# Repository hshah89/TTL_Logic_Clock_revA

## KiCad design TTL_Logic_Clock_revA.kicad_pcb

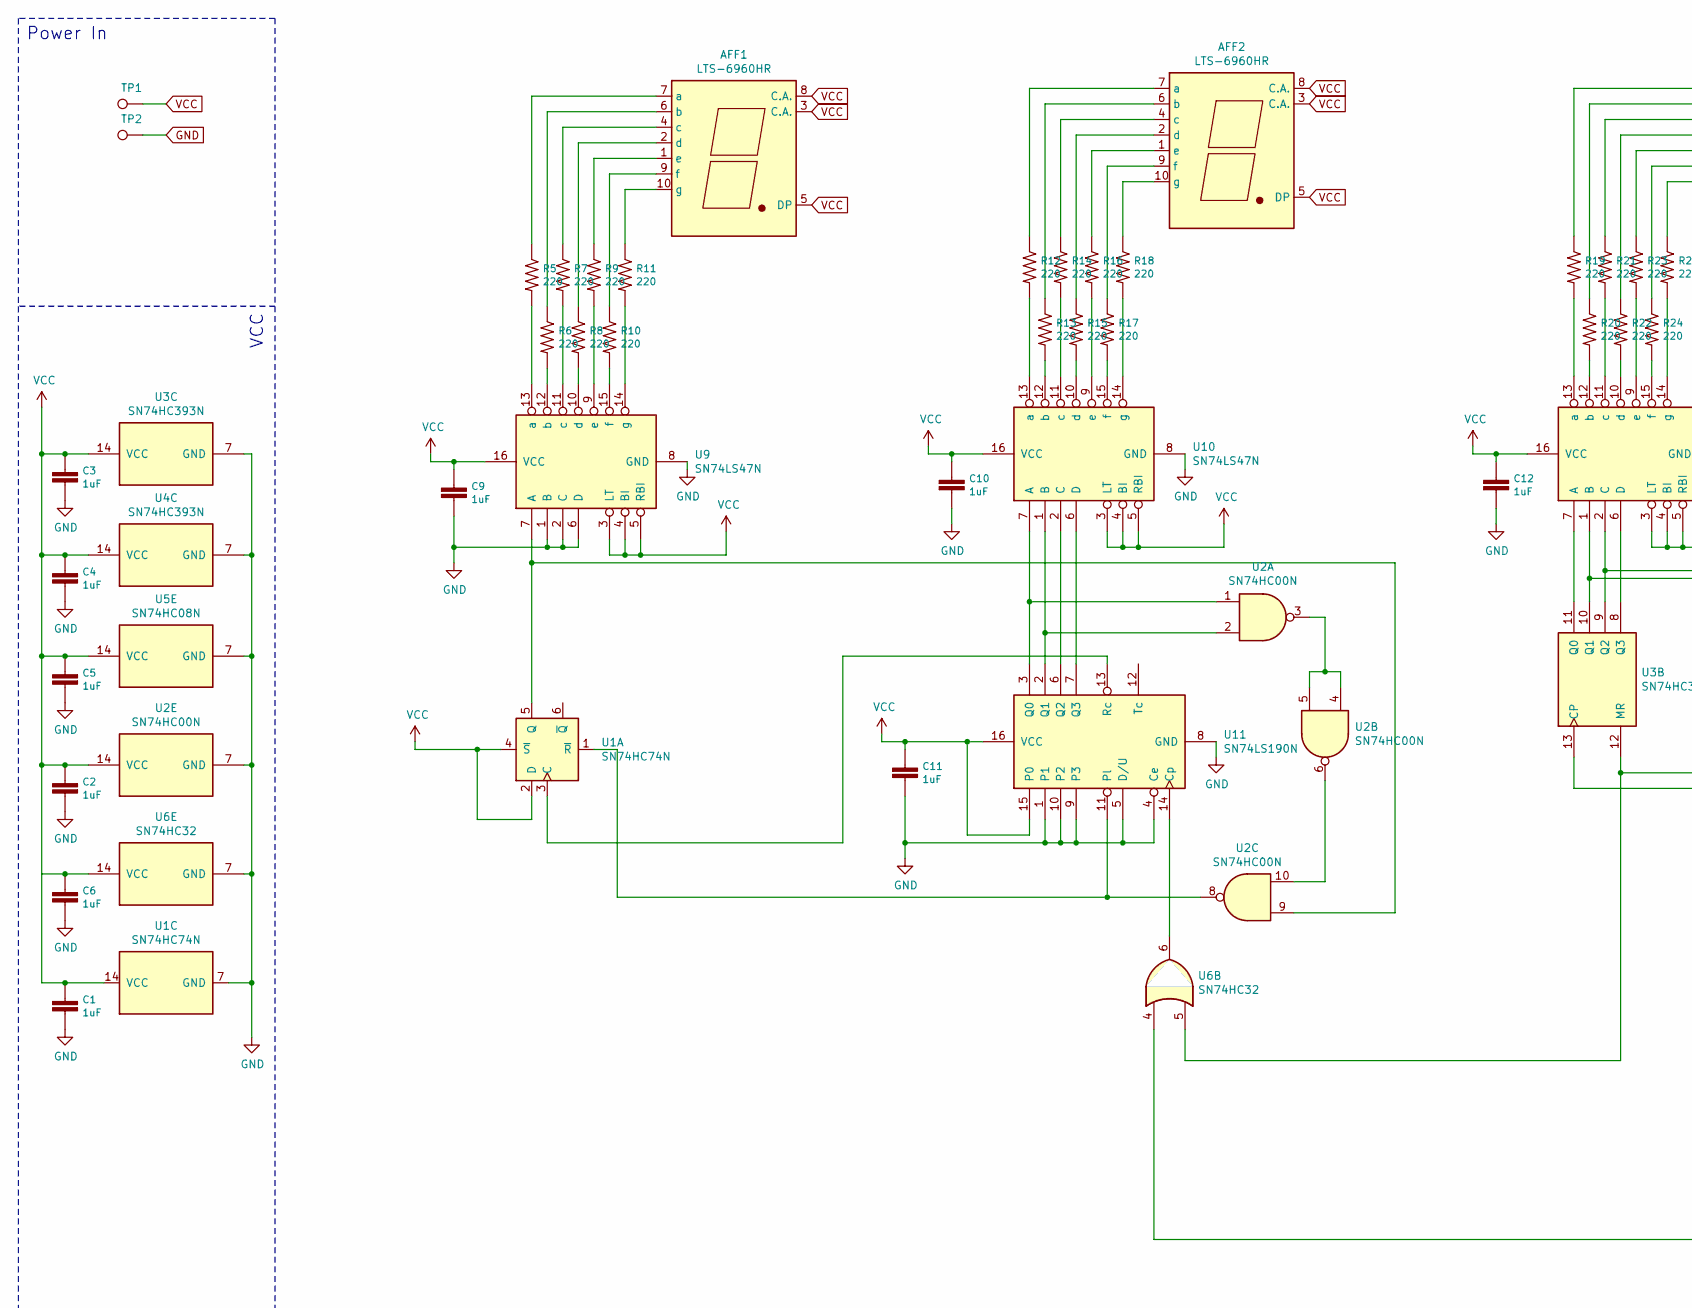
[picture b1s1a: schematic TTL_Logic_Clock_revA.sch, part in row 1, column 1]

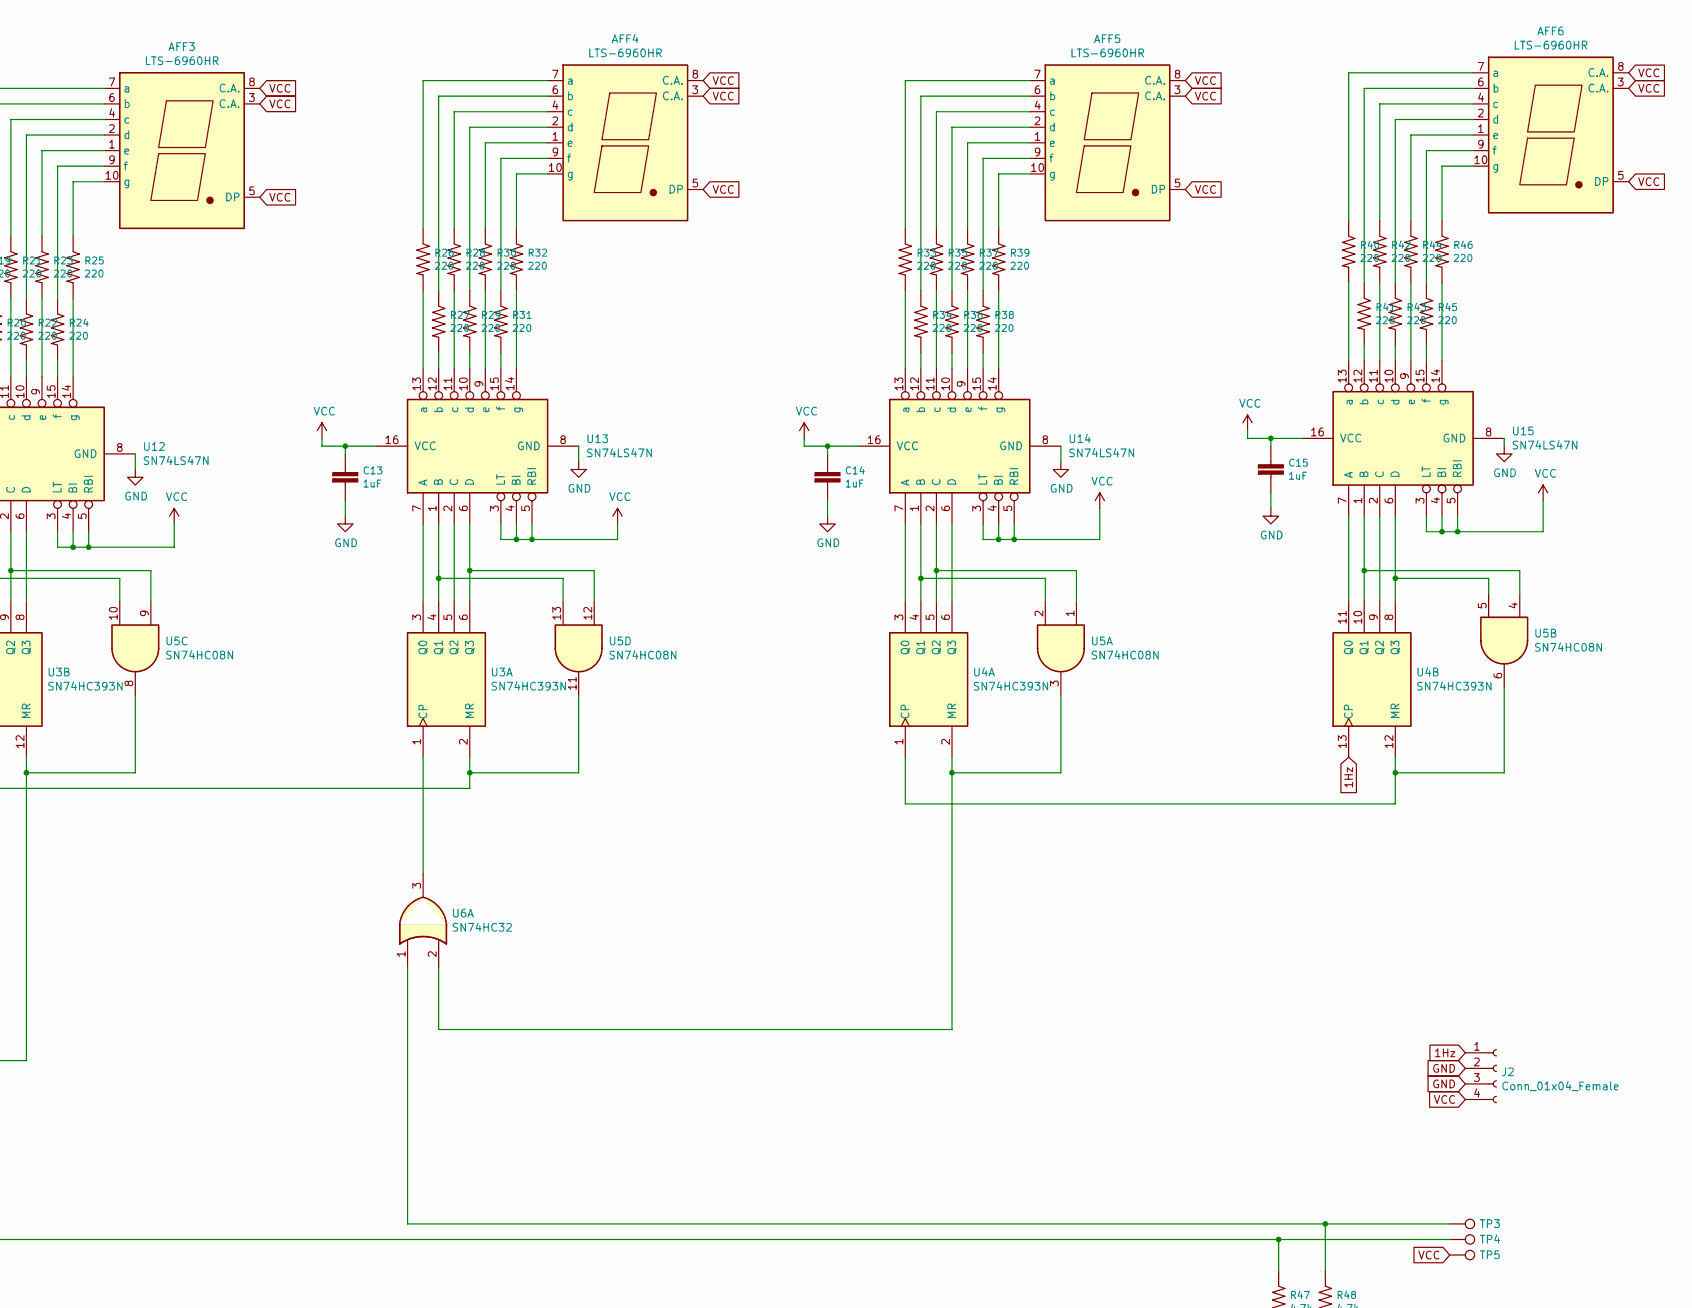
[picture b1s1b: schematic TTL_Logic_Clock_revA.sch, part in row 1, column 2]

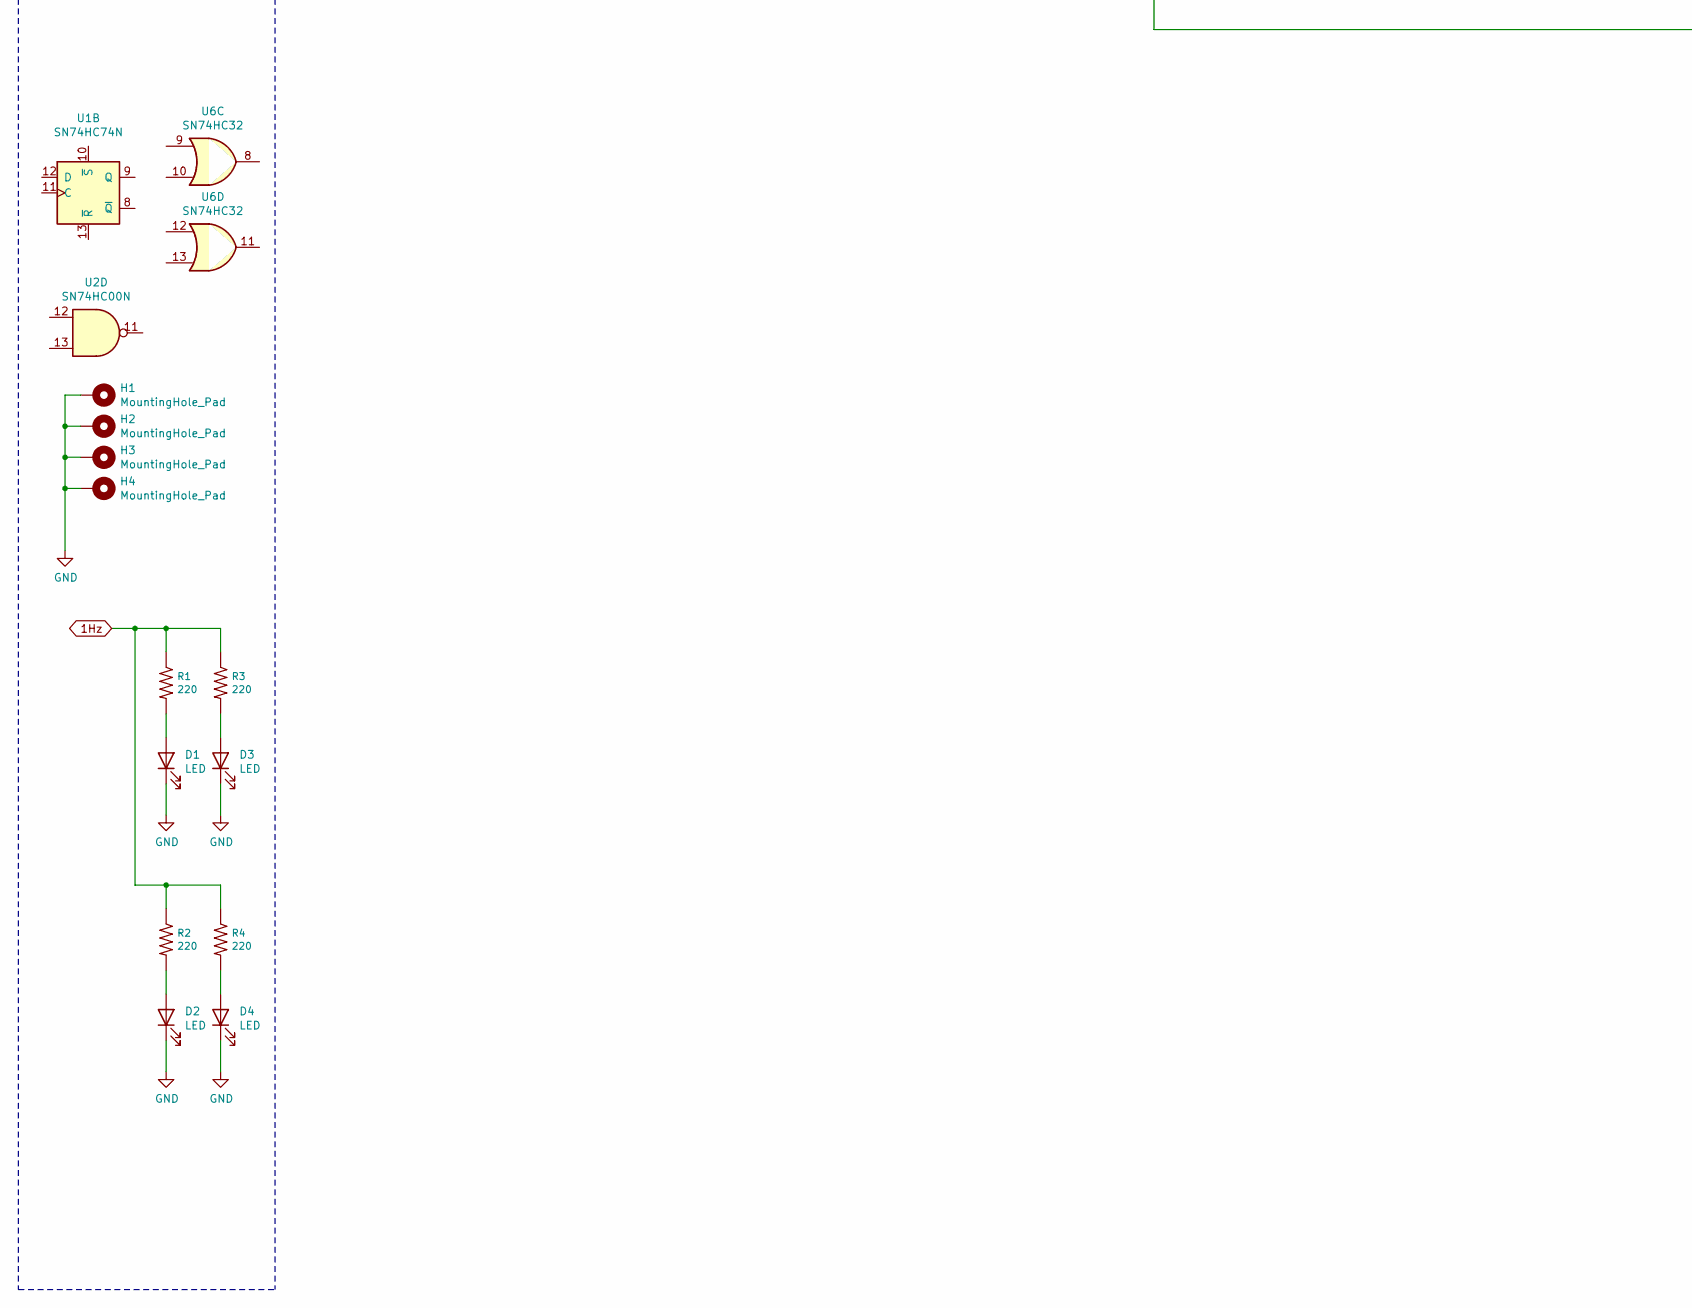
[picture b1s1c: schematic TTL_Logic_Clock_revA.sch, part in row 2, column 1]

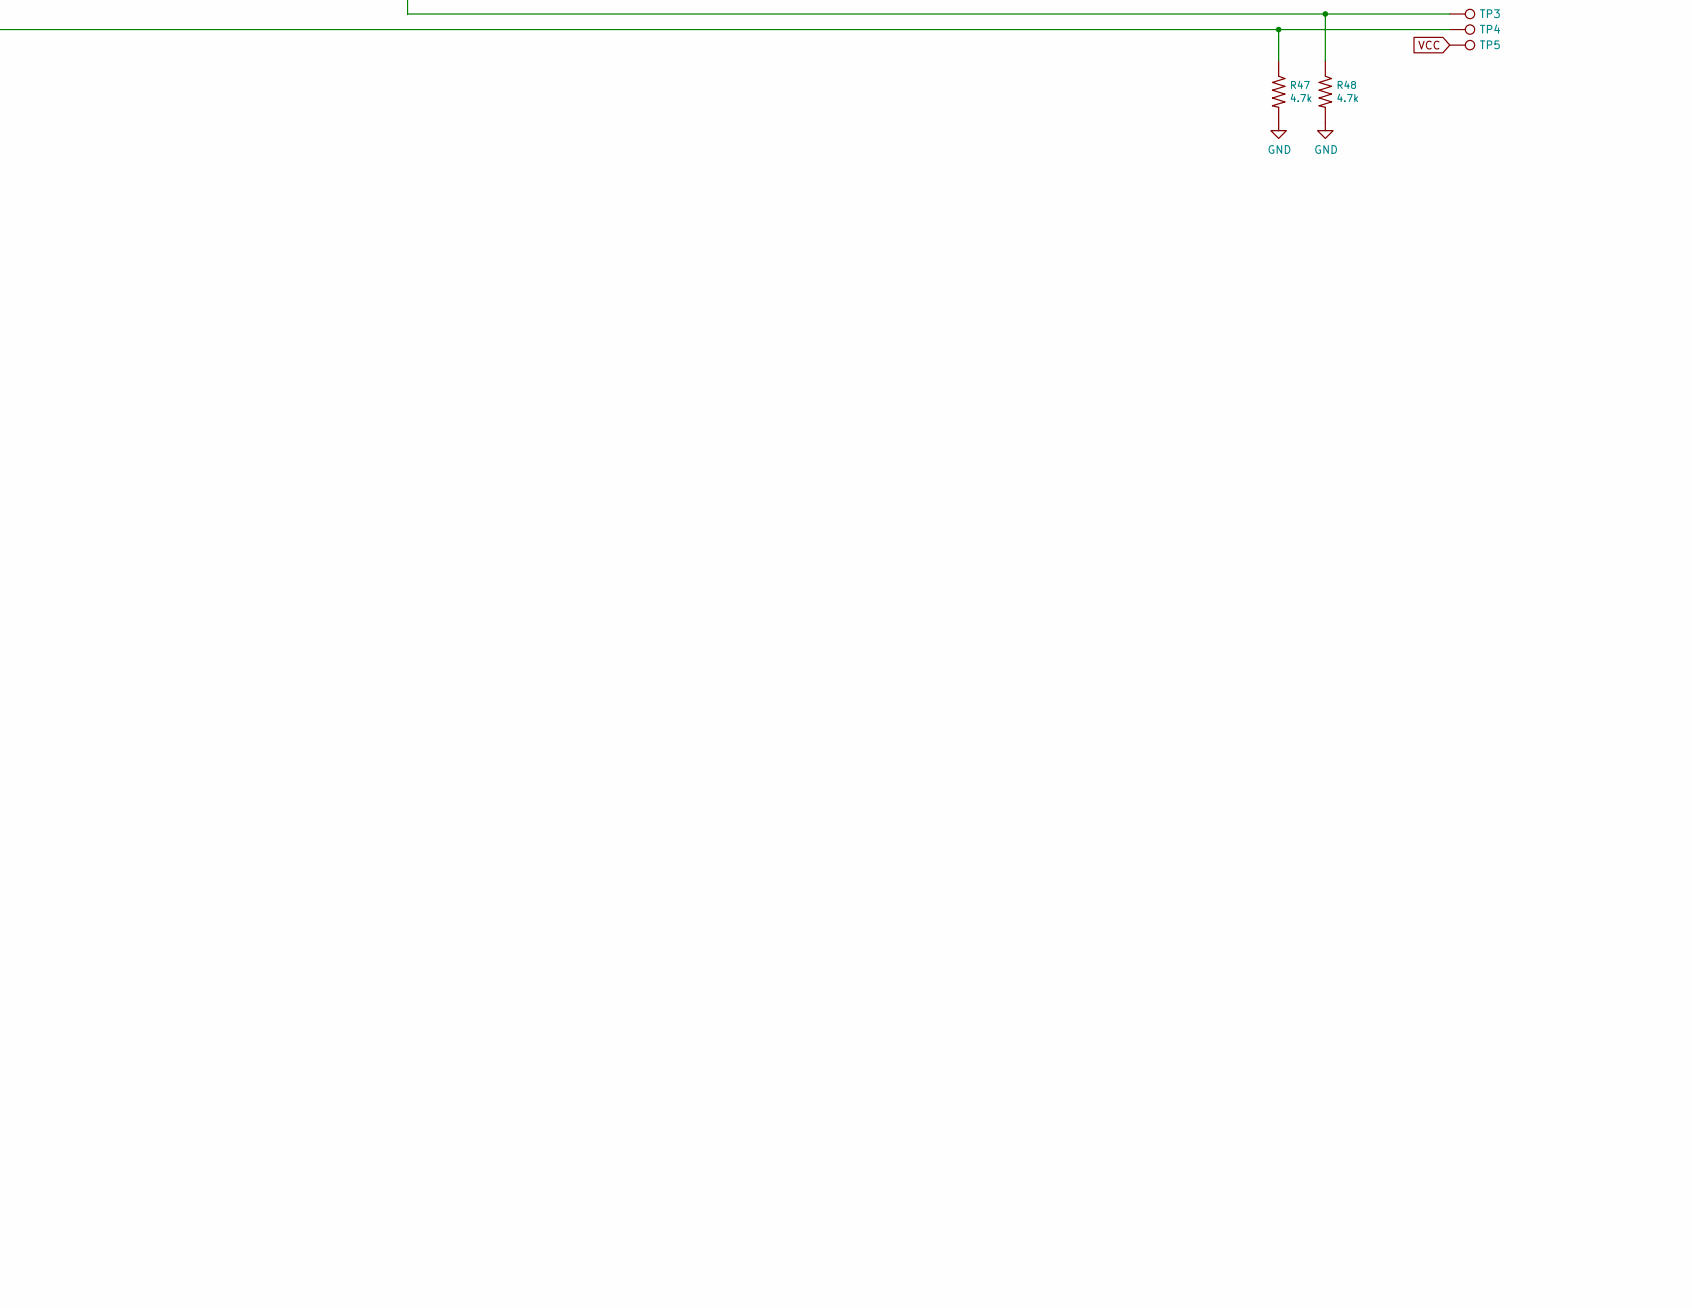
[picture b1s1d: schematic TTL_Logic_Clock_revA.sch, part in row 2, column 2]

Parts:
AFF1, AFF2, AFF3, AFF4, AFF5, AFF6: LTS-6960HR; 7SegmentLED_LTS6760_LTS6780
C1, C2, C3, C4, C5, C6, C9, C10, C11, C12, C13, C14, C15: 1uF; C_Disc_D3.8mm_W2.6mm_P2.50mm
D1, D2, D3, D4: LED; LED_D1.8mm_W3.3mm_H2.4mm
H1, H2, H3, H4: MountingHole_Pad; MountingHole_3.2mm_M3_Pad
J2: Conn_01x04_Female; PinSocket_1x04_P2.54mm_Horizontal
R1, R2, R3, R4, R5, R6, R7, R8, R9, R10, R11, R12, R13, R14, R15, R16, R17, R18, R19, R20, R21, R22, R23, R24, R25, R26, R27, R28, R29, R30, R31, R32, R33, R34, R35, R36, R37, R38, R39, R40, R41, R42, R43, R44, R45, R46: 220; R_Axial_DIN0204_L3.6mm_D1.6mm_P5.08mm_Horizontal
R47, R48: 4.7k; R_Axial_DIN0204_L3.6mm_D1.6mm_P5.08mm_Horizontal
TP1, TP2, TP3, TP4, TP5: TestPoint; TestPoint_Keystone_5015_Micro-Minature
U1: SN74HC74N; DIP-14_W7.62mm_Socket
U2: SN74HC00N; DIP-14_W7.62mm_Socket
U3, U4: SN74HC393N; DIP-14_W7.62mm_Socket
U5: SN74HC08N; DIP-14_W7.62mm_Socket
U6: SN74HC32; DIP-14_W7.62mm_Socket
U9, U10, U12, U13, U14, U15: SN74LS47N; DIP-16_W7.62mm_Socket
U11: SN74LS190N; DIP-16_W7.62mm_Socket

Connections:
1Hz: J2.1, R1.1, R2.1, R3.1, R4.1, U4.13 (CP)
GND: C1.1, C2.1, C3.1, C4.1, C5.1, C6.1, C9.2, C10.2, C11.2, C12.2, C13.2, C14.2, C15.2, D1.1 (K), D2.1 (K), D3.1 (K), D4.1 (K), H1.1, H2.1, H3.1, H4.1, J2.2, J2.3, R47.2, R48.2, TP2.1, U1.7 (GND), U2.7 (GND), U3.7 (GND), U4.7 (GND), U5.7 (GND), U6.7 (GND), U9.1 (B), U9.2 (C), U9.6 (D), U9.8 (GND), U10.8 (GND), U11.1, U11.4 (Ce), U11.5 (D/U), U11.8 (GND), U11.9 (P3), U11.10 (P2), U12.8 (GND), U13.8 (GND), U14.8 (GND), U15.8 (GND)
unnamed: AFF1.1 (e), R9.1
unnamed: AFF1.2 (d), R8.1
unnamed: AFF1.4 (c), R7.1
unnamed: AFF1.6 (b), R6.1
unnamed: AFF1.7 (a), R5.1
unnamed: AFF1.9 (f), R10.1
unnamed: AFF1.10 (g), R11.1
unnamed: AFF2.1 (e), R16.1
unnamed: AFF2.2 (d), R15.1
unnamed: AFF2.4 (c), R14.1
unnamed: AFF2.6 (b), R13.1
unnamed: AFF2.7 (a), R12.1
unnamed: AFF2.9 (f), R17.1
unnamed: AFF2.10 (g), R18.1
unnamed: AFF3.1 (e), R23.1
unnamed: AFF3.2 (d), R22.1
unnamed: AFF3.4 (c), R21.1
unnamed: AFF3.6 (b), R20.1
unnamed: AFF3.7 (a), R19.1
unnamed: AFF3.9 (f), R24.1
unnamed: AFF3.10 (g), R25.1
unnamed: AFF4.1 (e), R30.1
unnamed: AFF4.2 (d), R29.1
unnamed: AFF4.4 (c), R28.1
unnamed: AFF4.6 (b), R27.1
unnamed: AFF4.7 (a), R26.1
unnamed: AFF4.9 (f), R31.1
unnamed: AFF4.10 (g), R32.1
unnamed: AFF5.1 (e), R37.1
unnamed: AFF5.2 (d), R36.1
unnamed: AFF5.4 (c), R35.1
unnamed: AFF5.6 (b), R34.1
unnamed: AFF5.7 (a), R33.1
unnamed: AFF5.9 (f), R38.1
unnamed: AFF5.10 (g), R39.1
unnamed: AFF6.1 (e), R44.1
unnamed: AFF6.2 (d), R43.1
unnamed: AFF6.4 (c), R42.1
unnamed: AFF6.6 (b), R41.1
unnamed: AFF6.7 (a), R40.1
unnamed: AFF6.9 (f), R45.1
unnamed: AFF6.10 (g), R46.1
unnamed: D1.2 (A), R1.2
unnamed: D2.2 (A), R2.2
unnamed: D3.2 (A), R3.2
unnamed: D4.2 (A), R4.2
unnamed: R5.2, U9.13 (a)
unnamed: R6.2, U9.12 (b)
unnamed: R7.2, U9.11 (c)
unnamed: R8.2, U9.10 (d)
unnamed: R9.2, U9.9 (e)
unnamed: R10.2, U9.15 (f)
unnamed: R11.2, U9.14 (g)
unnamed: R12.2, U10.13 (a)
unnamed: R13.2, U10.12 (b)
unnamed: R14.2, U10.11 (c)
unnamed: R15.2, U10.10 (d)
unnamed: R16.2, U10.9 (e)
unnamed: R17.2, U10.15 (f)
unnamed: R18.2, U10.14 (g)
unnamed: R19.2, U12.13 (a)
unnamed: R20.2, U12.12 (b)
unnamed: R21.2, U12.11 (c)
unnamed: R22.2, U12.10 (d)
unnamed: R23.2, U12.9 (e)
unnamed: R24.2, U12.15 (f)
unnamed: R25.2, U12.14 (g)
unnamed: R26.2, U13.13 (a)
unnamed: R27.2, U13.12 (b)
unnamed: R28.2, U13.11 (c)
unnamed: R29.2, U13.10 (d)
unnamed: R30.2, U13.9 (e)
unnamed: R31.2, U13.15 (f)
unnamed: R32.2, U13.14 (g)
unnamed: R33.2, U14.13 (a)
unnamed: R34.2, U14.12 (b)
unnamed: R35.2, U14.11 (c)
unnamed: R36.2, U14.10 (d)
unnamed: R37.2, U14.9 (e)
unnamed: R38.2, U14.15 (f)
unnamed: R39.2, U14.14 (g)
unnamed: R40.2, U15.13 (a)
unnamed: R41.2, U15.12 (b)
unnamed: R42.2, U15.11 (c)
unnamed: R43.2, U15.10 (d)
unnamed: R44.2, U15.9 (e)
unnamed: R45.2, U15.15 (f)
unnamed: R46.2, U15.14 (g)
unnamed: R47.1, TP4.1, U6.4
unnamed: R48.1, TP3.1, U6.1
unnamed: U1.1 (~R), U2.8, U11.11 (Pl)
unnamed: U1.3 (C), U11.13 (Rc)
unnamed: U1.5 (Q), U2.9, U9.7 (A)
unnamed: U2.3, U2.4, U2.5
unnamed: U2.6, U2.10
unnamed: U3.1 (CP), U6.3
unnamed: U3.12 (MR), U5.8, U6.5
unnamed: U3.2 (MR), U3.13 (CP), U5.11
unnamed: U4.1 (CP), U4.12 (MR), U5.6
unnamed: U4.2 (MR), U5.3, U6.2
unnamed: U2.2, U10.1 (B), U11.2 (Q1)
unnamed: U10.2 (C), U11.6 (Q2)
unnamed: U10.6 (D), U11.7 (Q3)
unnamed: U2.1, U10.7 (A), U11.3 (Q0)
unnamed: U6.6, U11.14 (Cp)
unnamed: U3.10 (Q1), U5.10, U12.1 (B)
unnamed: U3.9 (Q2), U5.9, U12.2 (C)
unnamed: U3.8 (Q3), U12.6 (D)
unnamed: U3.11 (Q0), U12.7 (A)
unnamed: U3.4 (Q1), U5.13, U13.1 (B)
unnamed: U3.5 (Q2), U13.2 (C)
unnamed: U3.6 (Q3), U5.12, U13.6 (D)
unnamed: U3.3 (Q0), U13.7 (A)
unnamed: U4.4 (Q1), U5.2, U14.1 (B)
unnamed: U4.5 (Q2), U5.1, U14.2 (C)
unnamed: U4.6 (Q3), U14.6 (D)
unnamed: U4.3 (Q0), U14.7 (A)
unnamed: U4.10 (Q1), U5.4, U15.1 (B)
unnamed: U4.9 (Q2), U15.2 (C)
unnamed: U4.8 (Q3), U5.5, U15.6 (D)
unnamed: U4.11 (Q0), U15.7 (A)
VCC: AFF1.3 (C.A.), AFF1.5 (DP), AFF1.8 (C.A.), AFF2.3 (C.A.), AFF2.5 (DP), AFF2.8 (C.A.), AFF3.3 (C.A.), AFF3.5 (DP), AFF3.8 (C.A.), AFF4.3 (C.A.), AFF4.5 (DP), AFF4.8 (C.A.), AFF5.3 (C.A.), AFF5.5 (DP), AFF5.8 (C.A.), AFF6.3 (C.A.), AFF6.5 (DP), AFF6.8 (C.A.), C1.2, C2.2, C3.2, C4.2, C5.2, C6.2, C9.1, C10.1, C11.1, C12.1, C13.1, C14.1, C15.1, J2.4, TP1.1, TP5.1, U1.2 (D), U1.4 (~S), U1.14 (VCC), U2.14 (VCC), U3.14 (VCC), U4.14 (VCC), U5.14 (VCC), U6.14 (VCC), U9.3 (LT), U9.4 (BI), U9.5 (RBI), U9.16 (VCC), U10.3 (LT), U10.4 (BI), U10.5 (RBI), U10.16 (VCC), U11.15 (P0), U11.16 (VCC), U12.3 (LT), U12.4 (BI), U12.5 (RBI), U12.16 (VCC), U13.3 (LT), U13.4 (BI), U13.5 (RBI), U13.16 (VCC), U14.3 (LT), U14.4 (BI), U14.5 (RBI), U14.16 (VCC), U15.3 (LT), U15.4 (BI), U15.5 (RBI), U15.16 (VCC)

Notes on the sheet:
Power In
VCC

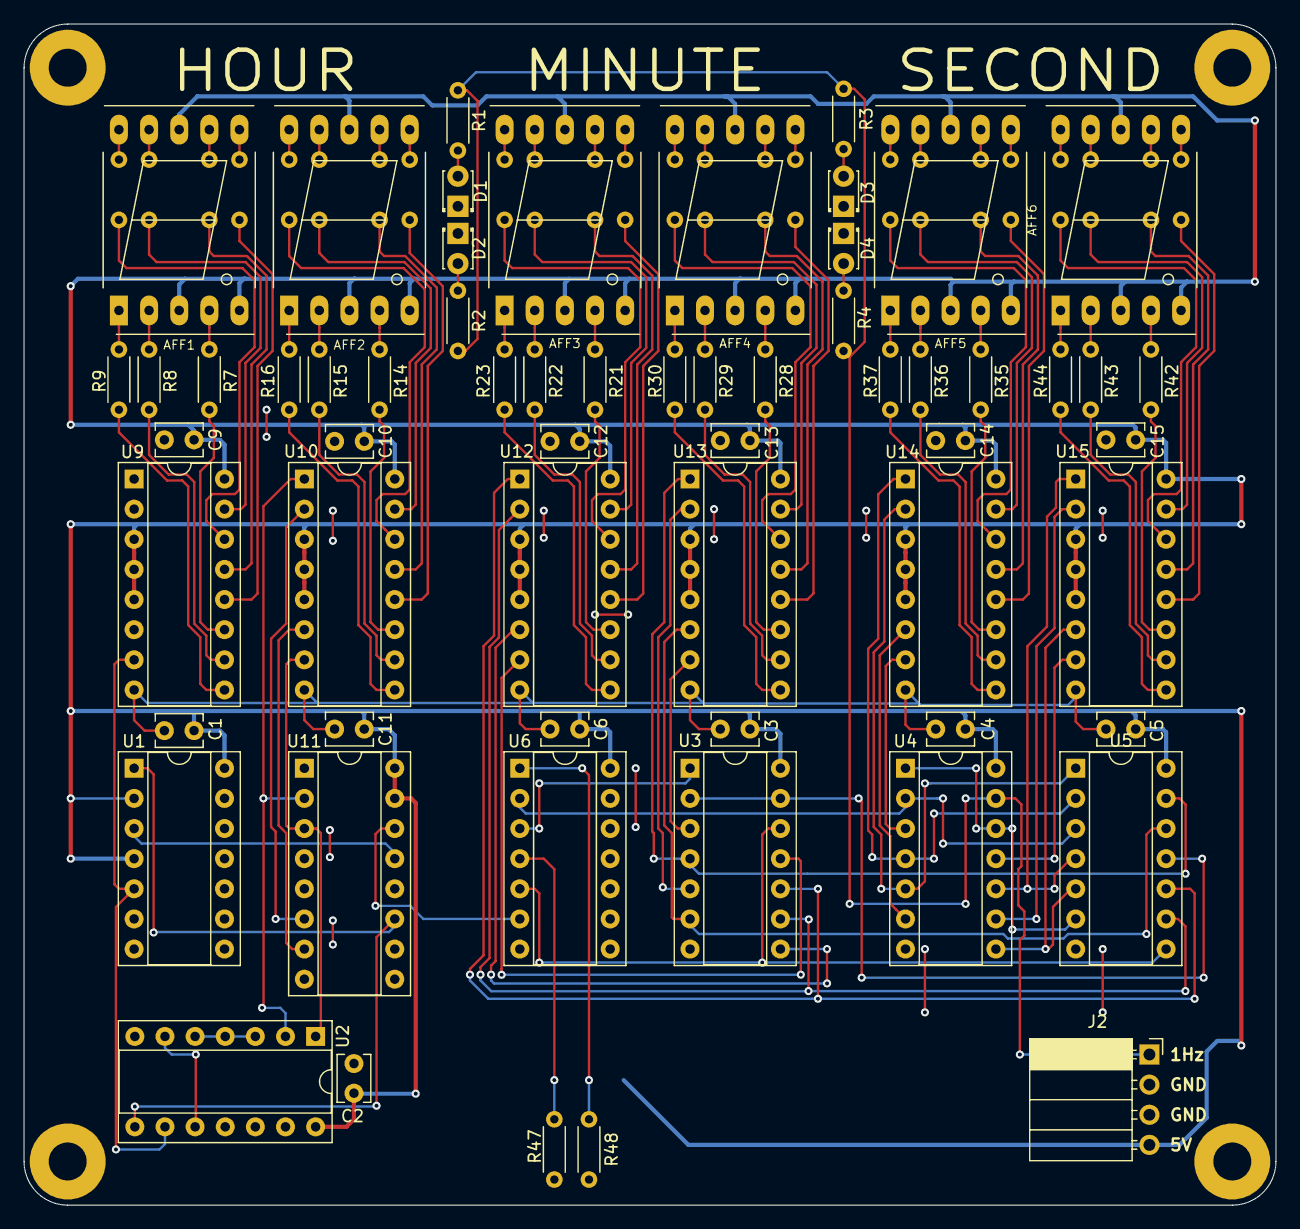
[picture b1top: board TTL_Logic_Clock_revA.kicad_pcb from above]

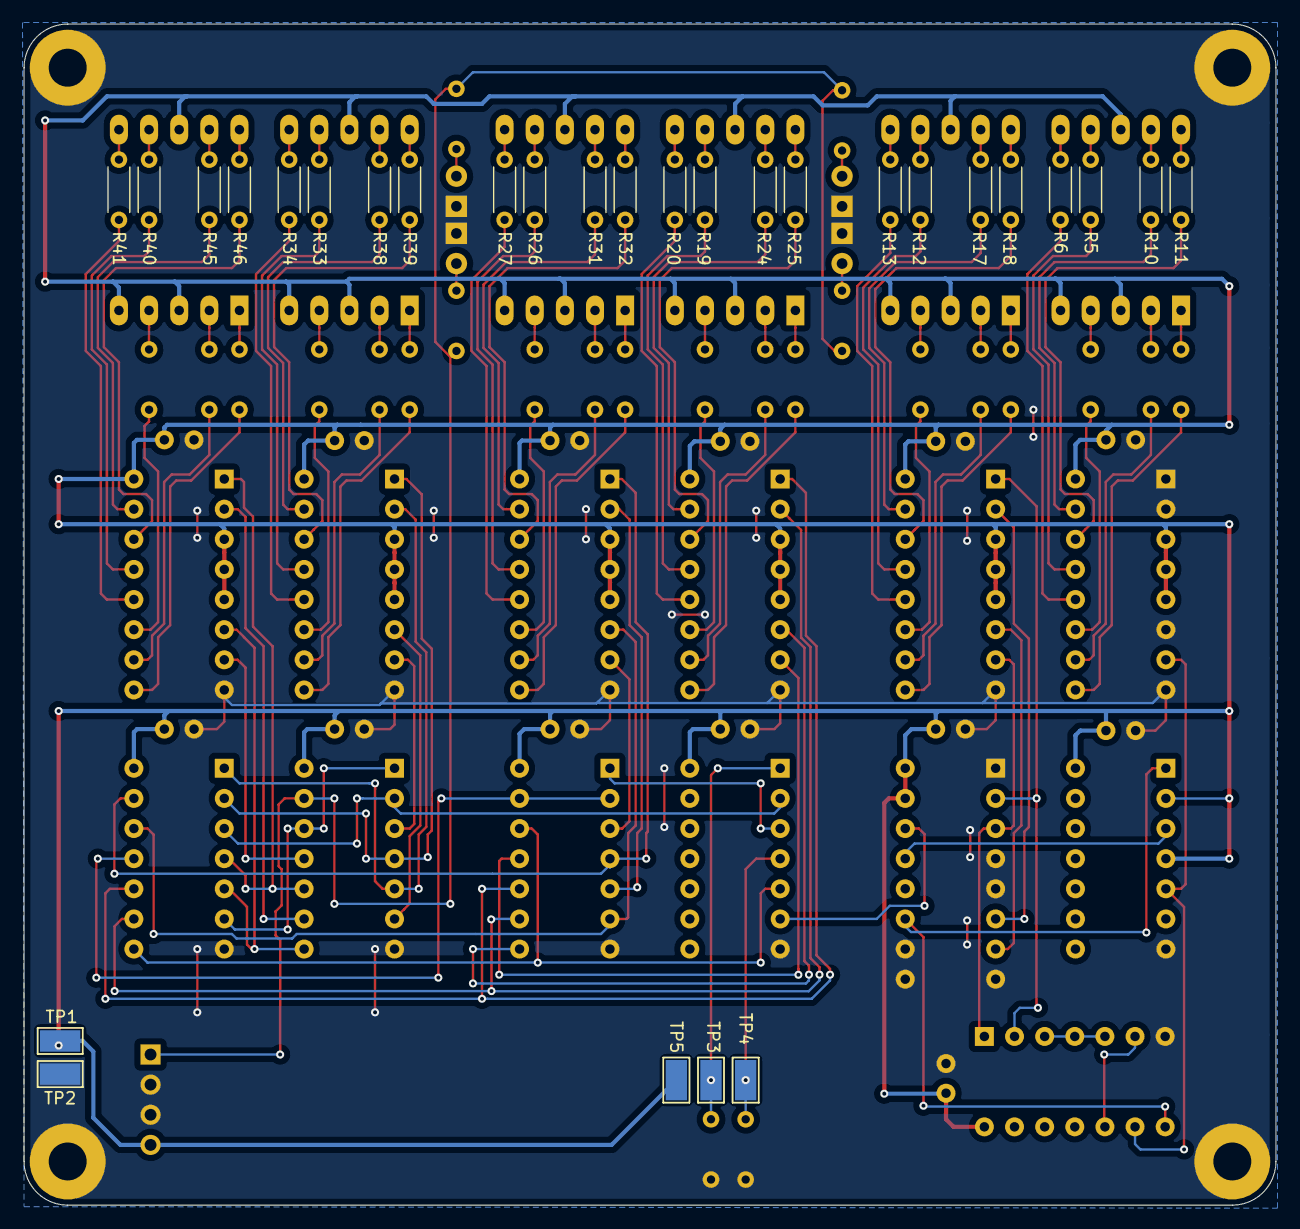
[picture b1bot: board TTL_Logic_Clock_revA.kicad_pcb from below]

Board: 2 copper layers, 105.5 x 99.6 mm, 94 parts (29 on the bottom side), 124 nets.

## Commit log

2021-01-28 new updates
2021-01-28 Revert "new updates"
    This reverts commit 53f30aa524d5c5c52be93e0d1f9b706b91b0ddee.
2021-02-01 added gerber files
